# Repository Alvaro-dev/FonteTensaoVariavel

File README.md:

# Fonte Tensão 12V
Projeto de uma Fonte de Tensão Variável de 3V a 12V, desenvolvido para a disciplina de Eletrônica para Computação, ministrada pelo Professor Dr. Eduardo do Valle Simões
# Circuito Falstad
<a href = "http://tinyurl.com/yclddzmd"> Circuito Falstad</a>

# Circuito EAGLE

<a href = "https://drive.google.com/file/d/1tgSCFVqVofuXs6VpP3hKhitnwWkWix8T/view?usp=sharing"> Vídeo Explicativo</a>

# Esquemático EAGLE

## Conversor Corrente Alternada de Alta Tensão para Corrente Alternada de Baixa Tensão
Ao usar um transformador de 127V AC para 24V AC, com a razão descrita abaixo, a tensão do circuito, fica adequada aos componentes usados na fonte, que são mais sensíveis a valores altos de tensão e suas variações. Quando há variação de fluxo na corrente primária (127V), na parte secundária, é gerada uma corrente induzida com um potencial elétrico menor (24V). O intervalo de oscilação sai de 127V a -127V para 24V a -24V. A razão obtida na fórmula abaixo, auxiliou a resolução da problemática no Falstad, para conseguir ajustar a tensão secundária do transformador.

## Conversor Corrente Alternada para Corrente Contínua
Como estamos lidando com uma corrente alternada (24V a -24V), é necessário uma estratégia para converter desse tipo de corrente elétrica para contínua, para o funcionamento adequado da fonte. Assim, usa-se uma ponte retificadora feita com diodos, cuja função é tornar a corrente unidirecional devido a propriedade do diodo, que permite o fluxo de corrente em apenas um sentido determinado. Por motivos de incompatibilidade com o Eagle e indisponibilidade no mercado, mas ainda avaliando a proporcionalidade do diodo/PCB, escolhemos a ponte retificadora KBPC1010 pois ela é compatível com o Eagle e está disponível na loja escolhida. 
Assim, a tensão na saída da ponte retificadora será uma unidirecional, porém instável para se usar dessa maneira na saída. Como a corrente nominal é, no máximo, de 1.205 A, usamos uma ponte retificadora de diodos que resiste a uma corrente de até 10 A, maior que o necessário, porém foi a ponte com menor especificação que encontramos na distribuidora.

## Filtragem de Corrente
A saída da ponte retificadora é instável, possuindo pequenas oscilações em sua voltagem, dessa forma forma será usado um capacitor conectado em paralelo com o output, com o objetivo de diminuir essas oscilações para a próxima parte do circuito. O objetivo de colcoar um capacitor, se baseia no fato do circuito precisar de tensão/corrente durante a parte na qual os valores de tais atributos estão baixos, necessitando que o capacitor se descarregue para manter uma margem confortável para o funcionamento geral do circuito.
O capacitor ao carregar e descarregar durante seu ciclo fornece um aumento linear da voltagem, filtrando o sinal e disponibilizando uma tensão mais estável. Dessa forma, escolhemos um capacitor de 470uF, valor ideal para manter uma corrente sem muitas oscilações.

## Regulador de Tensão
O Diodo Zener associado ao potenciômetro, conjuntamente com o Transistor NPN, permite que a tensão e corrente seja regulada e programada a partir de sua resistência variável.
- <b>Diodo Zener:</b> Ao ser conectado em paralelo, será responsável pela regulação da tensão máxima que será fornecida ao Potenciômetro. Esse componente atua filtrando a tensão somente quando for fornecido a ele uma tensão suficientemente maior do que a sua tensão nominal, 13V no caso deste projeto. Dessa forma, quando o Diodo Zener estiver ativo parte da corrente do circuito será absorvida e uma tensão 13V estável será fornecida ao Transistor. O Resistor  conectado será responsável por limitar a corrente que flui em direção ao Zener, tornando seguro o uso do modelo escolhido. Nota-se pelo simulador que há um pico de corrente de, aproximadamente, -1.5mA e que o Diodo está submetido a uma tensão de -13V, dissipando no máximo 19.5mW. Dessa forma, o componente escolhido (com especificações para 500mW) será suficiente.

- <b>Potenciômetro:</b> Resistor variável que permitirá regular a tensão elétrica de saída. Em conjunto com restante do circuito, o Potenciômetro foi devidamente projetado para fornecer uma tensão final no intervalo entre 3V e 12V, atendendo as especificações do projeto. Quando ajustado para uma resistência mínima, a tensão de saída será aproximadamente 12V. Analogamente, quando for regulado em sua resistência máxima a tensão fornecida será próxima de 3V. O Resistor  será responsável por regular a tensão fornecida ao transistor, adequando-a a 3V, quando o potenciômetro estiver com resistência máxima.

- <b>Transistor NPN:</b> Quando sobre ele é aplicada uma voltagem em sua base o Transistor passa a atuar em seu estado condutivo. Tem como papel, nesse circuito, amplificar a corrente, fornecendo ao circuito uma corrente, através do coletor, na ordem de 100 vezes maior do que a corrente base. Para atender ao requisitos do projeto (Fonte de Tensão com no máximo 100mA) foi escolhido um resistor de  para que a corrente final do circuito, quando regulado para 12V, permaneça nesse valor. Nota-se então que a corrente de base, e a corrente final possuirão os seguintes valores nos extremos:
  - 
  -   

Vale notar que há no Transistor uma queda de tensão de aproximadamente 715 mV quando a tensão de base for 13V e de 678 mV quando a tensão da base for, aproximadamente, 4.6V. É preciso considerar essa queda de tensão uma vez que a tensão final do circuito será o resultado da tensão de base subtraída da queda de tensão no Transistor.

# Orçamento dos materiais usados
Tabela com os preços dos componentes
|     Nome    |     Especificações    |     Preço    |
| :-------------: | :----------: | :-----------: |
| Transformador | Transformador Trafo 12V+12V 500mA – 110/220VAC | <a href = "https://www.baudaeletronica.com.br/transformador-trafo-12v-12v-500ma-110-220vac.html">R$ 22,23</a>|
| Resistor 1.5K   | Resistor 1.5K 5% (1/4W) | <a href = "https://www.baudaeletronica.com.br/resistor-1k5-5-1-4w.html">R$ 0,08</a> |
| Resistor 2.7K   | Resistor 2.7K 5% (1/4W) | <a href = "https://www.baudaeletronica.com.br/resistor-2k7-5-1-4w.html">R$ 0,08</a> |
| Resistor 2.2K   | Resistor 2.2K 5% (1/4W) | <a href = "https://www.baudaeletronica.com.br/resistor-2k2-5-1-4w.html">R$ 0,08</a> |
| Resistor 120R   | Resistor 120R 5% (1/4W) | <a href = "https://www.baudaeletronica.com.br/resistor-120r-5-1-4w.html">R$ 0,08</a> |
| LED | Led Difuso 5mm Vermelho | <a href = "https://www.eletrogate.com/led-difuso-5mm-vermelho">R$ 0,25</a> |
| Diodo Zener   | Diodo Zener BZX55C [13V / 0.5W] | <a href = "https://www.baudaeletronica.com.br/diodo-zener-bzx55c-13v-0-5w.html">R$ 0,09</a> |
| Capacitor   | Capacitor Eletrolítico 470uF / 35V | <a href = "https://www.baudaeletronica.com.br/capacitor-eletrolitico-470uf-35v.html">R$ 0,57</a> |
| Potenciômetro 5k   | Potenciômetro Linear de 5K (5000Ω) | <a href = "https://www.baudaeletronica.com.br/potenciometro-linear-de-5k-5000.html">R$ 1,45</a> |
| Ponte Retificadora KBPC1010* | Ponte Retificadora de 10A | <a href = "https://www.baudaeletronica.com.br/ponte-retificadora-kbpc1010.html"> R$ 3,79  </a> |
| Transistor   | Transistor NPN 2N3904 | <a href = "https://www.baudaeletronica.com.br/transistor-npn-2n3904.html">R$ 0,17</a> |
| Total   |  | R$ 28,87 |

* Poderíamos ter usado componentes mais baratos, mas devido ao fato do software Eagle/Loja não possuirem os modelos modelos mais adequados, escolhemos esse.

# Agradecimentos
Queremos agradecer ao professor Dr Eduardo Simões pela oportunidade de fazer o trabalho com as retificações necessárias, conforme especificado. Esperamos que, no futuro, poderemos usufruir novamente de alguma disciplina ministrada pelo professor, em um contexto cujo aprendizado não seja à distância.

Queremos também agradecer aos criadores do website: https://componentsearchengine.com/ por nos disponibilizar as libraries do EAGLE de graça.

# Contribuição
Alvaro José Lopes - 10873365

Paulo Henrique de Souza Soares - 11884713

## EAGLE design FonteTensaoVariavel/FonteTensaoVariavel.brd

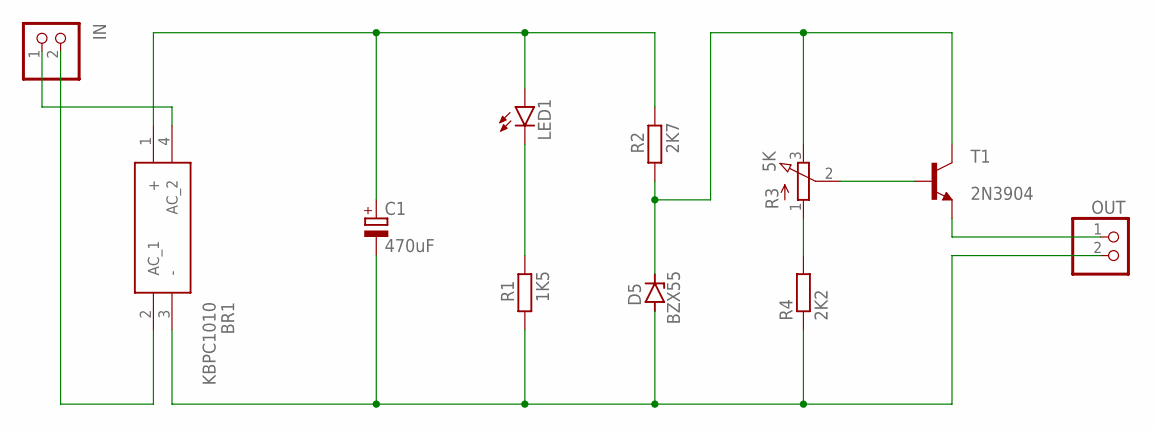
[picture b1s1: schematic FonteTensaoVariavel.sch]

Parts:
BR1: KBPC1010
C1: 470uF; E5-10,5
D5: BZX55; DO35Z10
IN: PINHD-1X2; 1X02
LED1: LED5MM
OUT: PINHD-1X2; 1X02
R1: 1K5; 0207/10
R2: 2K7; 0207/10
R3: 5K; 3RP/1610N
R4: 2K2; 0207/10
T1: 2N3904; TO92

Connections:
unnamed: BR1.4 (AC_2), IN.1
unnamed: BR1.3 (-), C1.-, D5.A, OUT.2, R1.1, R4.1
unnamed: BR1.2 (AC_1), IN.2
unnamed: BR1.1 (+), C1.+, LED1.A, R2.2
unnamed: LED1.K (C), R1.2
unnamed: D5.C, R2.1, R3.3 (E), T1.1 (C)
unnamed: OUT.1, T1.3 (E)
unnamed: R3.1 (A), R4.2
unnamed: R3.2 (S), T1.2 (B)

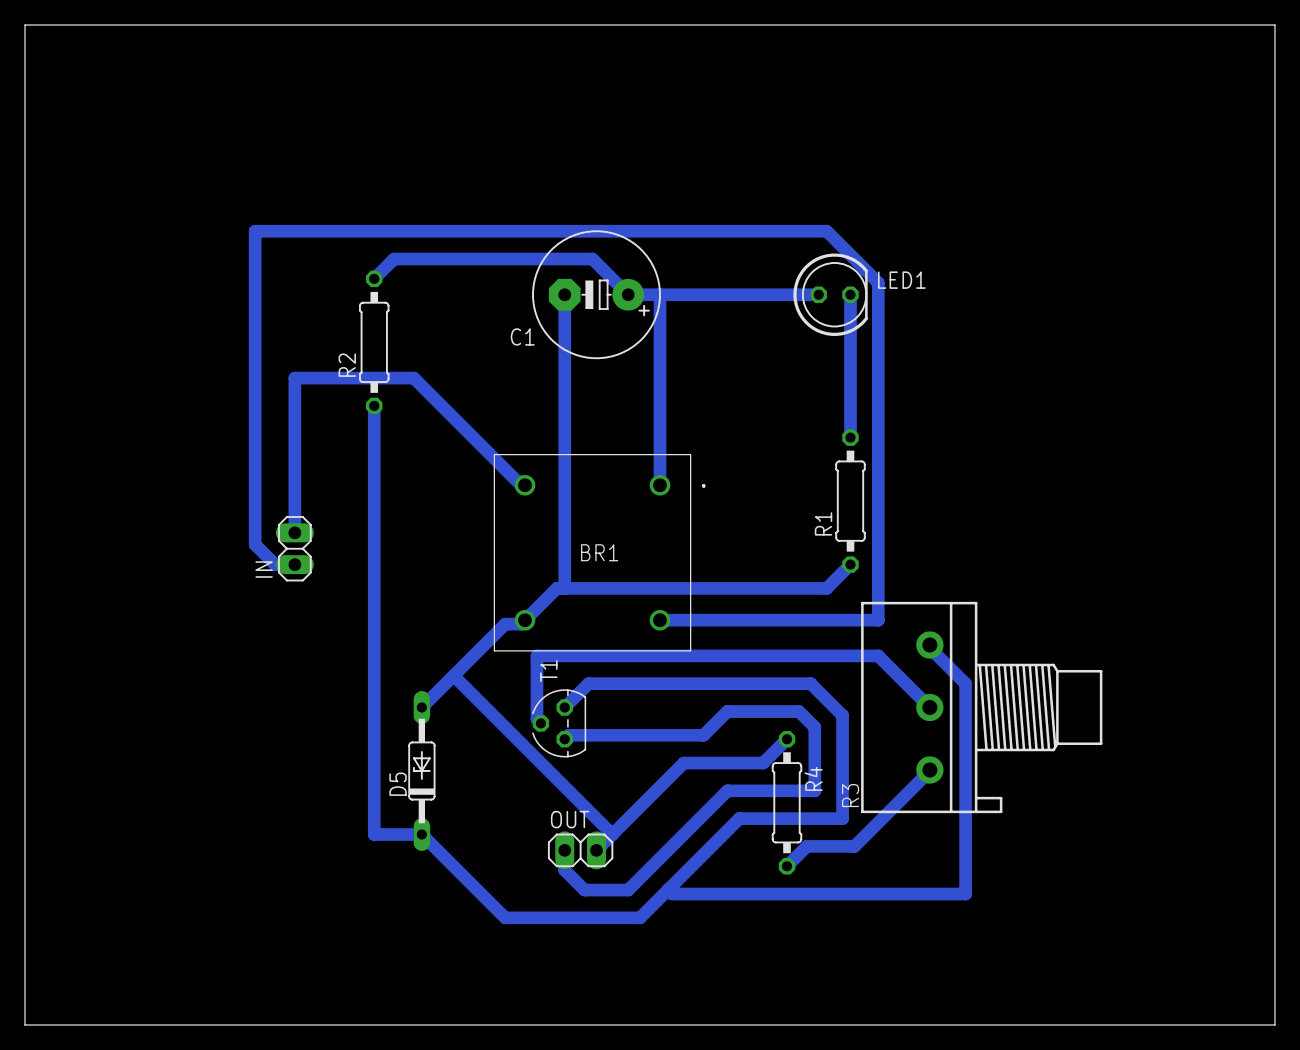
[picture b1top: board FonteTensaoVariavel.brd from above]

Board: 2 copper layers, 100.0 x 80.0 mm, 11 parts (0 on the bottom side), 9 nets.

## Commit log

2020-07-12 teste
